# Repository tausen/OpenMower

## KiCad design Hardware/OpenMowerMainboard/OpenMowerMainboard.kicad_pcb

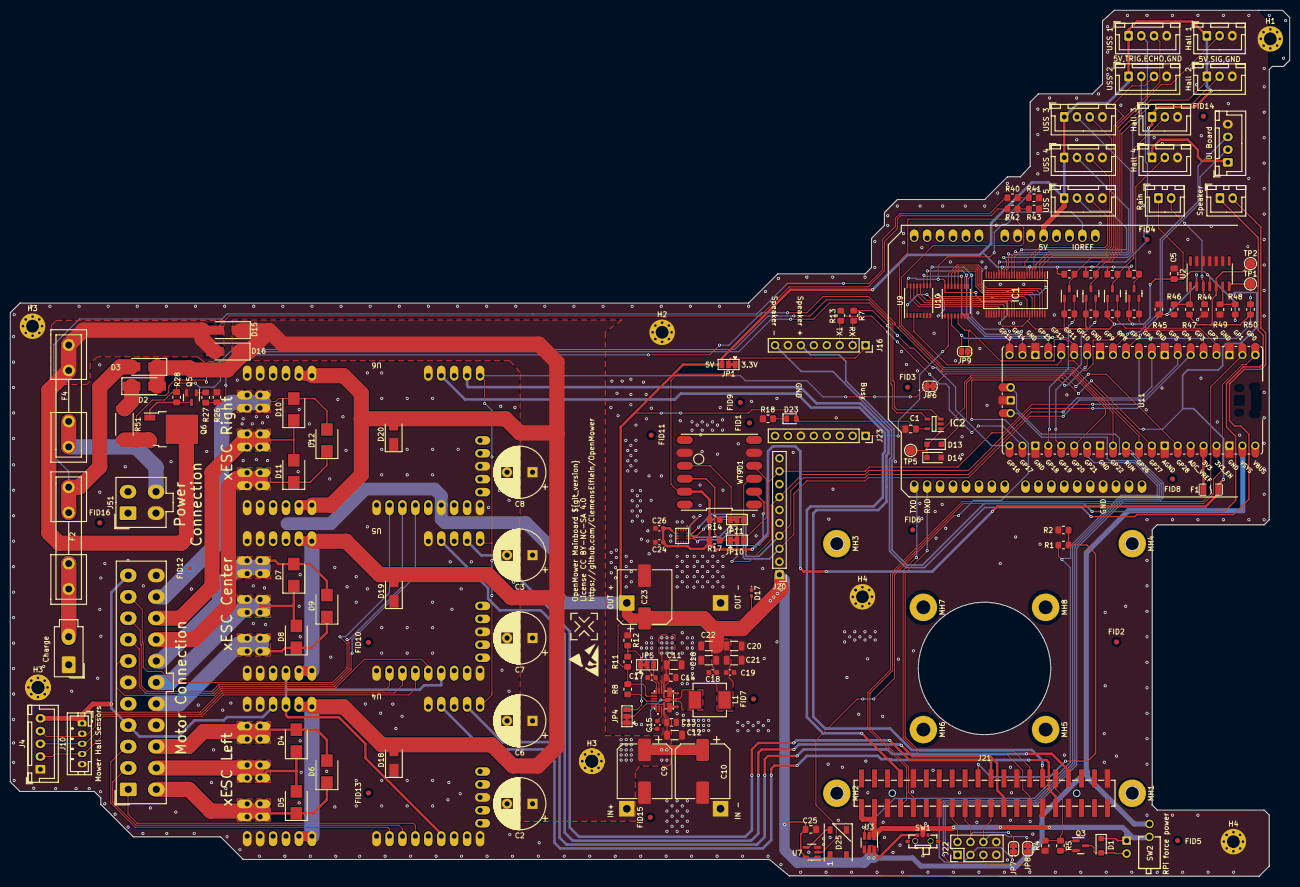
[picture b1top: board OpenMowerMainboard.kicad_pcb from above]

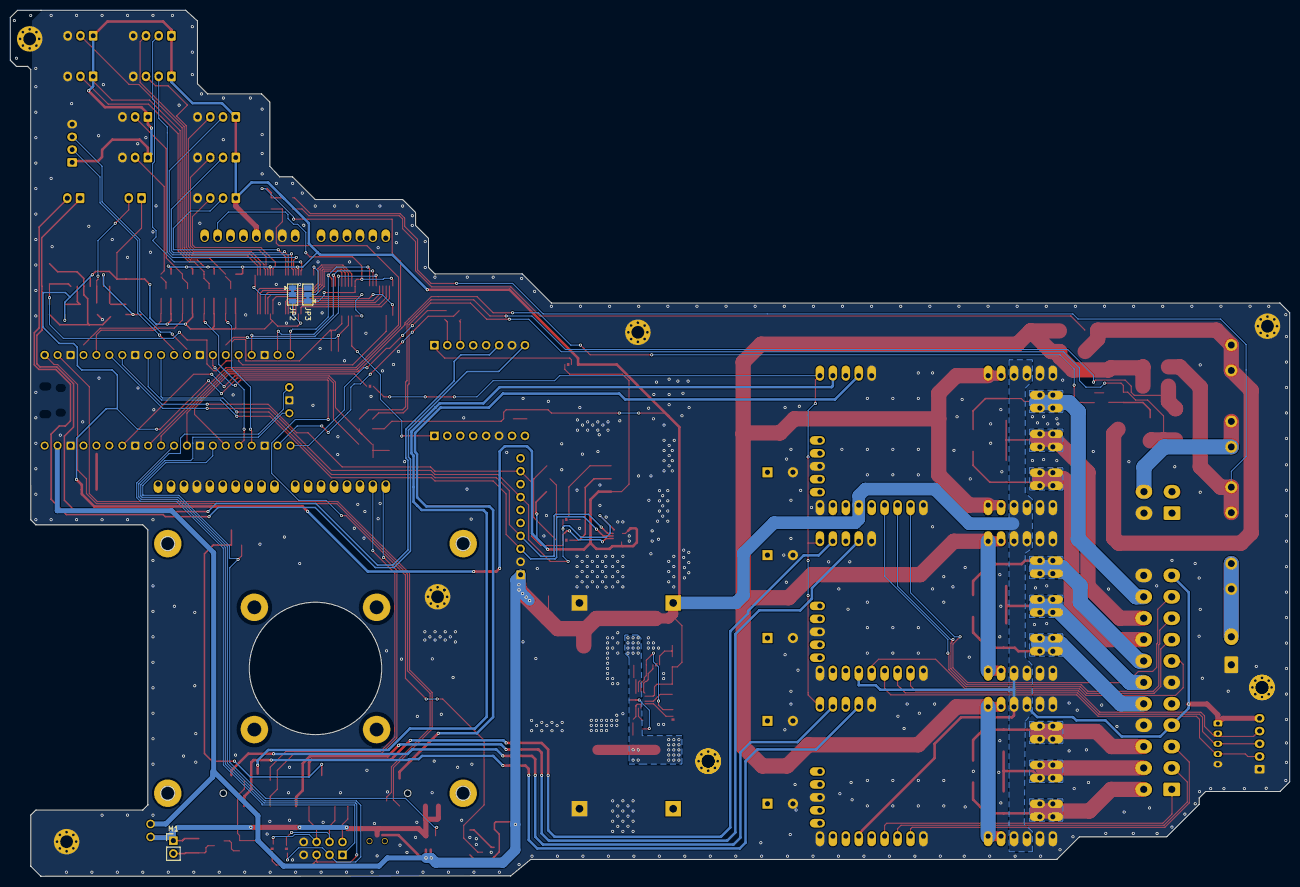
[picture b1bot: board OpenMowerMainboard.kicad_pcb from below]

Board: 2 copper layers, 251.2 x 170.0 mm, 182 parts (3 on the bottom side), 130 nets.

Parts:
AC1201: LSM6DSOTR; LGA-14_2.5X3X0.86_
C1, C5, C25: 100nF; C_0805_2012Metric_Pad1.18x1.45mm_HandSolder
C2, C3, C6, C7, C8: 220uF; CP_Radial_D10.0mm_P5.00mm
C9, C23: 680uF; CP_Elec_10x12.5
C10: DNP; CP_Elec_10x12.5
C11, C12: 4.7uF; C_1206_3216Metric
C13, C14: 1uF; C_0805_2012Metric
C15, C18, C19, C24, C26: 0.1uF; C_0603_1608Metric
C16, C20, C21, C22: 22uF; C_1206_3216Metric
C17: 2.2uF; C_0603_1608Metric
D1: D_Schottky; D_SOD-123F
D2, D3, D15, D16: D_Schottky; D_SMA_Handsoldering
D4, D5, D6, D7, D8, D9, D10, D11, D12: DNP; D_SMB
D13, D14: DNP; D_SOD-123F
D17: DNP; D_0402_1005Metric_Pad0.77x0.64mm_HandSolder
D18, D19, D20: DNP; D_SMA
D23: LED; LED_0805_2012Metric
D25: WS2812B; LED_WS2812B_PLCC4_5.0x5.0mm_P3.2mm
F1: nSMD035-16V; F1206
F2, F4: Fuse; Fuseholder5x20_horiz_open_inline_Type-I
FID1, FID2, FID3, FID4, FID5, FID6, FID7, FID8, FID9, FID10, FID11, FID12, FID13, FID14, FID15, FID16: Fiducial; Fiducial_1mm_Mask2mm
H1, H2, H3, H3#2, H3#3, H4, H4#2: MountingHole_Pad; MountingHole_2.5mm_Pad_Via
IC1: 74ALVC164245DGG,11; SOP50P810X120-48N
IC2: TSC101CILT; SOT95P280X145-5N
IC3: MAX20405AFOF_VY+T; MAX2040
J1: Conn_02x11_Top_Bottom; Molex_Mini-Fit_Jr_5566-22A_2x11_P4.20mm_Vertical
J3: Conn_01x02; Molex_Mini-Fit_Jr_5566-02A_2x01_P4.20mm_Vertical
J4: Conn_01x05; JST_XH_B5B-XH-A_1x05_P2.50mm_Vertical
J5, J6, J7, J8, J9, J19: Conn_01x04; JST_XH_B4B-XH-A_1x04_P2.50mm_Vertical
J10: Conn_01x05; JST_PH_B5B-PH-K_1x05_P2.00mm_Vertical
J11, J12, J13, J14: Conn_01x03_Male; JST_XH_B3B-XH-A_1x03_P2.50mm_Vertical
J16, J23: Conn_01x08; PinSocket_1x08_P2.54mm_Vertical
J17, J18: Conn_01x02; JST_XH_B2B-XH-A_1x02_P2.50mm_Vertical
J20: Conn_01x10_Female; PinHeader_1x10_P2.54mm_Vertical
J21: Raspberry_Pi_2_3; HDR-SMD_40P-P2.54-V-F-R2-C20-S8.8-EH
J22: Conn_02x04_Odd_Even; PinHeader_2x04_P2.54mm_Vertical
J51: Conn_01x04; Molex_Mini-Fit_Jr_5566-04A_2x02_P4.20mm_Vertical
JP1, JP2, JP3, JP4, JP5: SolderJumper_3_Bridged12; SolderJumper-3_P1.3mm_Bridged12_Pad1.0x1.5mm
JP6, JP7, JP8: SolderJumper_2_Bridged; SolderJumper-2_P1.3mm_Bridged_RoundedPad1.0x1.5mm
JP9: SolderJumper_2_Open; SolderJumper-2_P1.3mm_Open_RoundedPad1.0x1.5mm
JP10, JP11: I2C_OR_TTL; SolderJumper-3_P1.3mm_Bridged12_Pad1.0x1.5mm
L1: 4.7uH 5A; L_Vishay_IHLP-2525
LOGO1: LOGO; ESD-Logo_6.6x6mm_SilkScreen
LOGO2: ESD-Logo_6.6x6mm_SilkScreen
M1: Fan; PinHeader_1x02_P2.54mm_Vertical
MH1, MH2, MH3, MH4, MH5, MH6, MH7, MH8: MountingHole_2.7mm_M2.5_Pad
Q3, Q5, Q13, Q14, Q15, Q16: BSS138; SOT-23
Q6: Q_PMOS_GDS; TO-252-2
R1, R2, R4, R12, R26, R28, R40, R42, R48, R50: 10k; R_0805_2012Metric_Pad1.20x1.40mm_HandSolder
R3, R6, R7, R9, R10, R13, R15, R16, R18, R19, R20, R41, R43, R45, R47: 1k; R_0805_2012Metric_Pad1.20x1.40mm_HandSolder
R5, R27: 150; R_0805_2012Metric_Pad1.20x1.40mm_HandSolder
R8: DNP; R_0805_2012Metric_Pad1.20x1.40mm_HandSolder
R11: 53k6 1%; R_0805_2012Metric_Pad1.20x1.40mm_HandSolder
R14, R17, R49: 4k7; R_0805_2012Metric_Pad1.20x1.40mm_HandSolder
R44, R46: 47k; R_0805_2012Metric_Pad1.20x1.40mm_HandSolder
R51: 0.003R; R_2512_6332Metric_Pad1.40x3.35mm_HandSolder
RP?: Raspberry_Pi_2_3; raspberrypi_2_3
SW1: MK-11C04-G013; SW-SMD_MK-11C04-G013
SW2: DA-01BP; SW-TH_DA-01BP
TP1, TP2, TP5: TestPoint; TestPoint_Pad_D2.0mm
U1: DNP; LM2596S_MODULE
U2: MCP604; SOIC-14_3.9x8.7mm_P1.27mm
U3: SIP32509DT; SOT-23-6_Handsoldering
U4, U5, U6: xESC2
U7: SN74LV1T34DBV; SOT-23-5
U9, U10: 74HC4051; SSOP-16_4.4x5.2mm_P0.65mm
U11: Pico; Raspberry_Pi_Pico_SMT_THT
WT901: Conn_02x06_Female; WT901
XA1: Arduino_Uno_Shield

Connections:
+3V3: AC1201.5 (VDDIO), AC1201.8 (VDD), C5.2, C24.1, C26.1, D13.1 (K), F1.2, IC1.31 (VCC(A)_1), IC1.42 (VCC(A)_2), J17.1, JP1.1 (A), JP2.3 (B), JP3.1 (A), Q13.1 (G), Q14.1 (G), Q15.1 (G), Q16.1 (G), R3.1, R9.1, R14.2, R15.1, R17.2, R19.1, R48.2, U2.4 (V+), U9.16 (VCC), U10.16 (VCC), WT901.a2 (VCC), WT901.b2 (VCC), XA1.IORF (IOREF)
+5V: C1.1, C16.1, C18.1, C19.1, C20.1, C21.1, C22.1, C23.1, C25.1, D17.2 (A2), D23.2 (A), D25.1 (VDD), IC1.7 (VCC(B)_1), IC1.18 (VCC(B)_2), IC2.5 (VCC), IC3.13 (OUT), J1.4, J1.11, J4.5, J5.1, J6.1, J7.1, J8.1, J9.1, J10.1, J11.1, J12.1, J13.1, J14.1, J19.1, J20.1, JP1.3 (B), L1.2, R6.1, R8.2, R10.1, R11.2, R16.1, R20.1, SW1.1, SW2.2, U1.3 (OUT+), U3.5 (VIN), U3.6 (VIN), U4.5V, U5.5V, U6.5V, U7.5 (VCC), U11.39 (VSYS), XA1.5V1 (5V)
/CHARGE_CURRENT: D13.2 (A), D14.1 (K), IC2.1 (OUT), TP5.1, U11.34 (GPIO28_ADC2)
/ESCs/ESC_SHUTDOWN: JP6.1 (A), U11.26 (GPIO20)
/ESCs/MC_HALL_U: J4.2, J10.4, U5.4 (HALL_U)
/ESCs/MC_HALL_V: J4.3, J10.3, U5.5 (HALL_V)
/ESCs/MC_HALL_W: J4.4, J10.2, U5.6 (HALL_W)
/ESCs/MC_PHASE_U: D7.2 (A2), D9.2 (A2), J1.18, U5.U
/ESCs/MC_PHASE_V: D7.1 (A1), D8.2 (A2), J1.17, U5.V
/ESCs/MC_PHASE_W: D8.1 (A1), D9.1 (A1), J1.16, U5.W
/ESCs/MC_RX: J21.24 (~CE0/GPIO8), U5.14 (NCS/RX)
/ESCs/MC_TEMP: J1.7, U5.3 (TEMPERATURE)
/ESCs/MC_TX: J21.21 (MISO0/GPIO9), U5.12 (MOSI/TX)
/ESCs/ML_HALL_U: J1.1, U4.4 (HALL_U)
/ESCs/ML_HALL_V: J1.2, U4.5 (HALL_V)
/ESCs/ML_HALL_W: J1.3, U4.6 (HALL_W)
/ESCs/ML_PHASE_U: D4.2 (A2), D6.2 (A2), J1.14, U4.U
/ESCs/ML_PHASE_V: D4.1 (A1), D5.2 (A2), J1.13, U4.V
/ESCs/ML_PHASE_W: D5.1 (A1), D6.1 (A1), J1.12, U4.W
/ESCs/ML_RX: J21.32 (PWM0/GPIO12), U4.14 (NCS/RX)
/ESCs/ML_TX: J21.33 (PWM1/GPIO13), U4.12 (MOSI/TX)
/ESCs/MR_HALL_U: J1.8, U6.4 (HALL_U)
/ESCs/MR_HALL_V: J1.9, U6.5 (HALL_V)
/ESCs/MR_HALL_W: J1.10, U6.6 (HALL_W)
/ESCs/MR_PHASE_U: D10.2 (A2), D12.2 (A2), J1.21, U6.U
/ESCs/MR_PHASE_V: D10.1 (A1), D11.2 (A2), J1.20, U6.V
/ESCs/MR_PHASE_W: D11.1 (A1), D12.1 (A1), J1.19, U6.W
/ESCs/MR_RX: J21.7 (GCLK0/GPIO4), U6.14 (NCS/RX)
/ESCs/MR_TX: J21.29 (GCLK1/GPIO5), U6.12 (MOSI/TX)
/GPS/RXD: J21.27 (ID_SD/GPIO0), XA1.D1 (D1_TX0)
/GPS/TXD: J21.28 (ID_SC/GPIO1), XA1.D0 (D0_RX0)
/IMU/MISO: AC1201.1 (SDO/SA0), J20.7, JP11.2 (C), U11.6 (GPIO4)
/IMU/MOSI: AC1201.14 (SDA), J20.4, U11.10 (GPIO7)
/IMU/SCK: AC1201.13 (SCL), J20.3, U11.9 (GPIO6)
/IMU/~CS: AC1201.12 (CS), J20.9, JP10.2 (C), U11.7 (GPIO5)
/RAIN_DETECTED: JP9.1 (A), R50.2, TP1.1, U2.7, U10.5 (A5)
/RaspberryPi/PICO_RESET: J22.1, U11.30 (RUN)
/RaspberryPi/PICO_SWCLK: J22.5, JP8.1 (A), U11.41 (SWCLK)
/RaspberryPi/PICO_SWDIO: J22.3, JP7.1 (A), U11.43 (SWDIO)
/RaspberryPi/POWER_EN: R1.1, U3.3 (ENABLE), U11.27 (GPIO21)
/RaspberryPi/RASPI_FAN_ON: J21.31 (GCLK2/GPIO6), R4.2, R5.1
/RaspberryPi/RASPI_POWER: D1.1 (K), J21.2 (5V), J21.4 (5V), M1.1 (+), SW1.C, SW2.1, U3.1 (VOUT), U3.2 (VOUT)
/RaspberryPi/UART0_RXD: J21.10 (GPIO15/RXD), U11.1 (GPIO0)
/RaspberryPi/UART0_TXD: J21.8 (GPIO14/TXD), U11.2 (GPIO1)
/RobotConnectors/CHARGE_SHUNT_MINUS: IC2.4 (VM), Q6.3 (S), R28.1, R51.2
/RobotConnectors/CHARGE_SHUNT_PLUS: D2.1 (K), IC2.3 (VP), R51.1
/RobotConnectors/ENABLE_CHARGE: R26.1, R27.1, U11.29 (GPIO22)
/RobotConnectors/HALL_SWITCH_1: Q13.2 (S), R3.2, U11.24 (GPIO18)
/RobotConnectors/HALL_SWITCH_1_5V: J11.2, Q13.3 (D), R6.2
/RobotConnectors/HALL_SWITCH_2: Q14.2 (S), R9.2, U11.25 (GPIO19)
/RobotConnectors/HALL_SWITCH_2_5V: J12.2, Q14.3 (D), R10.2
/RobotConnectors/HALL_SWITCH_3: Q15.2 (S), R15.2, U11.5 (GPIO3)
/RobotConnectors/HALL_SWITCH_3_5V: J13.2, Q15.3 (D), R16.2
/RobotConnectors/HALL_SWITCH_4: Q16.2 (S), R19.2, U11.4 (GPIO2)
/RobotConnectors/HALL_SWITCH_4_5V: J14.2, Q16.3 (D), R20.2
/RobotConnectors/LED_RX: J19.2, U11.11 (GPIO8)
/RobotConnectors/LED_TX: J19.3, U11.12 (GPIO9)
/RobotConnectors/RAIN-: J17.2, R44.2, U2.3 (+)
/RobotConnectors/SPEAKER_MINUS: J16.8, J18.2
/RobotConnectors/SPEAKER_PLUS: J16.6, J18.1
/RobotConnectors/USS_1_ECHO: IC1.47 (1A0), U10.15 (A2)
/RobotConnectors/USS_1_ECHO_5V: IC1.2 (1B0), J5.3
/RobotConnectors/USS_1_TRIGGER: IC1.30 (2A4), U9.15 (A2)
/RobotConnectors/USS_1_TRIGGER_5V: IC1.19 (2B4), J5.2
/RobotConnectors/USS_2_ECHO: IC1.46 (1A1), U10.14 (A1)
/RobotConnectors/USS_2_ECHO_5V: IC1.3 (1B1), J6.3
/RobotConnectors/USS_2_TRIGGER: IC1.32 (2A3), U9.14 (A1)
/RobotConnectors/USS_2_TRIGGER_5V: IC1.17 (2B3), J6.2
/RobotConnectors/USS_3_ECHO: IC1.44 (1A2), U10.13 (A0)
/RobotConnectors/USS_3_ECHO_5V: IC1.5 (1B2), J7.3
/RobotConnectors/USS_3_TRIGGER: IC1.33 (2A2), U9.13 (A0)
/RobotConnectors/USS_3_TRIGGER_5V: IC1.16 (2B2), J7.2
/RobotConnectors/USS_4_ECHO: IC1.43 (1A3), U10.12 (A3)
/RobotConnectors/USS_4_ECHO_5V: IC1.6 (1B3), J8.3
/RobotConnectors/USS_4_TRIGGER: IC1.35 (2A1), U9.12 (A3)
/RobotConnectors/USS_4_TRIGGER_5V: IC1.14 (2B1), J8.2
/RobotConnectors/USS_5_ECHO: IC1.41 (1A4), U10.1 (A4)
/RobotConnectors/USS_5_ECHO_5V: IC1.8 (1B4), J9.3
/RobotConnectors/USS_5_TRIGGER: IC1.36 (2A0), U9.1 (A4)
/RobotConnectors/USS_5_TRIGGER_5V: IC1.13 (2B0), J9.2
/RobotConnectors/V_BATTERY: D15.2 (A), D16.2 (A), F4.2, Q6.2 (D), R42.2
/RobotConnectors/V_CHARGE: D3.2 (A), F2.1, R40.2
/pico/MUX_ADDRESS_0: U9.11 (S0), U10.11 (S0), U11.17 (GPIO13)
/pico/MUX_ADDRESS_1: U9.10 (S1), U10.10 (S1), U11.19 (GPIO14)
/pico/MUX_ADDRESS_2: U9.9 (S2), U10.9 (S2), U11.20 (GPIO15)
/pico/MUX_INPUT: JP9.2 (B), U10.3 (A), U11.15 (GPIO11)
/pico/MUX_OUTPUT: U9.3 (A), U11.16 (GPIO12)
/pico/SOUND_BUSY: J23.1, U10.2 (A6)
/pico/SOUND_RX: R13.1, U11.22 (GPIO17)
/pico/SOUND_TX: R7.2, U11.21 (GPIO16)
/pico/V_CHARGE: R40.1, R41.2, U11.31 (GPIO26_ADC0)
/pico/V_IN: R42.1, R43.2, U11.32 (GPIO27_ADC1)
GND: AC1201.2 (SDX), AC1201.3 (SCX), AC1201.6 (GND_1), AC1201.7 (GND_2), C1.2, C2.2, C3.2, C5.1, C6.2, C7.2, C8.2, C9.2, C10.2, C11.2, C12.2, C13.2, C14.2, C16.2, C17.2, C18.2, C19.2, C20.2, C21.2, C22.2, C23.2, C24.2, C25.2, C26.2, D14.2 (A), D17.1 (A1), D18.1 (A1), D19.1 (A1), D20.1 (A1), D25.3 (VSS), H1.1, H2.1, H3.1, H3#2.1, H3#3.1, H4.1, H4#2.1, IC1.4 (GND_1), IC1.9 (1B5), IC1.10 (GND_2), IC1.11 (1B6), IC1.12 (1B7), IC1.15 (GND_3), IC1.21 (GND_4), IC1.25 (~2OE), IC1.26 (2A7), IC1.27 (2A6), IC1.28 (GND_5), IC1.29 (2A5), IC1.34 (GND_6), IC1.39 (GND_7), IC1.45 (GND_8), IC1.48 (~1OE), IC2.2 (GND), IC3.4 (PGND_1), IC3.5 (PGND_2), IC3.7 (PGND_3), IC3.8 (PGND_4), IC3.10 (GND), J1.6, J1.15, J1.22, J3.1, J4.1, J5.4, J6.4, J7.4, J8.4, J9.4, J10.5, J11.3, J12.3, J13.3, J14.3, J16.7, J19.4, J20.2, J21.6 (GND), J21.9 (GND), J21.14 (GND), J21.20 (GND), J21.25 (GND), J21.30 (GND), J21.34 (GND), J21.39 (GND), J22.7, J22.8, J23.6, J51.3, JP2.1 (A), JP3.3 (B), JP4.1 (A), Q3.2 (S), Q5.2 (S), R2.1, R4.1, R12.1, R18.1, R26.2, R41.1, R43.1, R44.1, R45.1, R49.2, U1.1 (IN-), U1.4 (OUT-), U2.9 (-), U2.10 (+), U2.11 (V-), U2.12 (+), U2.13 (-), U3.4 (GND), U4.GND, U5.GND, U6.GND, U7.3 (GND), U9.6 (~E), U9.7 (VEE), U9.8 (GND), U10.6 (~E), U10.7 (VEE), U10.8 (GND), U11.3 (GND), U11.8 (GND), U11.13 (GND), U11.18 (GND), U11.23 (GND), U11.28 (GND), U11.33 (AGND), U11.38 (GND), U11.42 (SWGND), WT901.a5 (GND), WT901.b5 (GND), XA1.GND1 (GND), XA1.GND2 (GND), XA1.GND3 (GND)
unnamed: D1.2 (A), M1.2 (-), Q3.3 (D)
unnamed: D23.1 (K), R18.2
unnamed: D25.4 (DIN), U7.4 (Y)
unnamed: IC1.1 (1DIR), JP2.2 (C)
unnamed: IC1.24 (2DIR), JP3.2 (C)
unnamed: C17.1, IC3.11 (BIAS), JP4.3 (B), JP5.3 (B)
unnamed: C15.1, IC3.2 (BST)
unnamed: IC3.12 (FB_1), IC3.20 (FB_2), JP5.2 (C)
unnamed: C15.2, IC3.6 (LX_1), IC3.19 (LX_2), L1.1
unnamed: IC3.15 (PGOOD), R8.1
unnamed: IC3.16 (SYNC), JP4.2 (C)
unnamed: IC3.17 (SYNCOUT_1), IC3.18 (SYNCOUT_2)
unnamed: F2.2, J3.2
unnamed: J16.1, JP1.2 (C)
unnamed: J16.2, R7.1
unnamed: J16.3, R13.2
unnamed: J21.16 (GPIO23), J22.2
unnamed: J21.18 (GPIO24), J22.4, JP7.2 (B)
unnamed: J21.22 (GPIO25), J22.6, JP8.2 (B)
unnamed: J21.19 (MOSI0/GPIO10), R1.2, R2.2
unnamed: F4.1, J51.4
unnamed: JP5.1 (A), R11.1, R12.2
unnamed: JP6.2 (B), U4.11 (MISO), U5.11 (MISO), U6.11 (MISO)
unnamed: JP10.1 (A), R17.1, WT901.b3 (SCL)
unnamed: JP10.3 (B), WT901.a4 (TX)
unnamed: JP11.1 (A), R14.1, WT901.b4 (SDA)
unnamed: JP11.3 (B), WT901.a3 (RX)
unnamed: Q3.1 (G), R5.2
unnamed: Q5.3 (D), Q6.1 (G), R28.2
unnamed: Q5.1 (G), R27.2
unnamed: R46.1, R47.1, U2.1
unnamed: R45.2, R46.2, U2.2 (-)
unnamed: R47.2, R50.1, TP2.1, U2.5 (+)
unnamed: R48.1, R49.1, U2.6 (-)
unnamed: F1.1, U11.36 (3V3)
unnamed: U7.2 (A), U11.14 (GPIO10)
V_BATT: C2.1, C3.1, C6.1, C7.1, C8.1, C9.1, C10.1, C11.1, C12.1, C13.1, C14.1, D2.2 (A), D3.1 (K), D15.1 (K), D16.1 (K), D18.2 (A2), D19.2 (A2), D20.2 (A2), IC3.1 (EN), IC3.3 (SUP_1), IC3.9 (SUP_2), U1.2 (IN+), U4.VM (VIN), U5.VM (VIN), U6.VM (VIN)

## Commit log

2024-06-01 Initial mainboard for Worx Landroid WR105SI
    Moved components and a few connectors around to make the mainboard fit
    in the Worx Landroid WR105SI. No functional changes (hopefully).
    Mounting holes are TBD.
2024-06-01 mainboard: squeeze bottom mid slightly
    Slightly reduce board height near bottom mid. Should give a bit more
    freedom when placing the board in the Landroid.
2024-06-08 mainboard: no mounting holes, squeeze connectors
    Remove mounting holes and squeeze upper right connectors
2024-06-09 mainboard: remove unused area in middle of board
2024-06-13 mainboard: fix J16-J23 distance
    Make distance between J16 and J23 fit the DFplayer again
2024-06-23 mainboard: landroid battery connector
2024-07-23 KiCAD 8 in CI
2024-07-23 deploy: 79106db2f6259f560fb081b19e94f5f0a04c8e92
2024-08-15 added user 6 layer to pcb
2024-08-15 mainboard: turbocase compatibility
    - Mounting holes for mounting PCB in case
    - Raspberry Pi 4 footprint for turbocase connector cutouts
    - Raspberry Pi 4 mounting hole footprint changed

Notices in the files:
Hardware/OpenMowerMainboard/OpenMowerMainboard.kicad_pcb:
License CC BY-NC-SA 4.0
